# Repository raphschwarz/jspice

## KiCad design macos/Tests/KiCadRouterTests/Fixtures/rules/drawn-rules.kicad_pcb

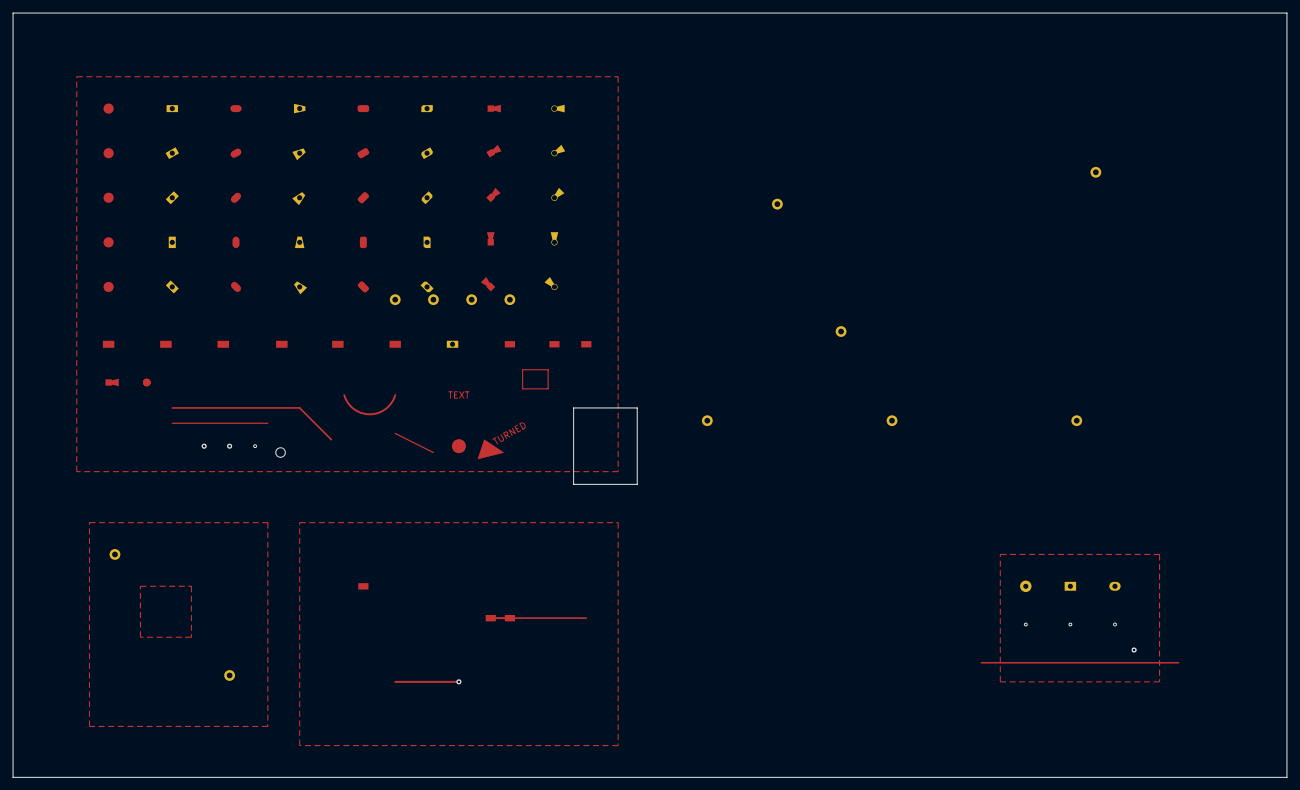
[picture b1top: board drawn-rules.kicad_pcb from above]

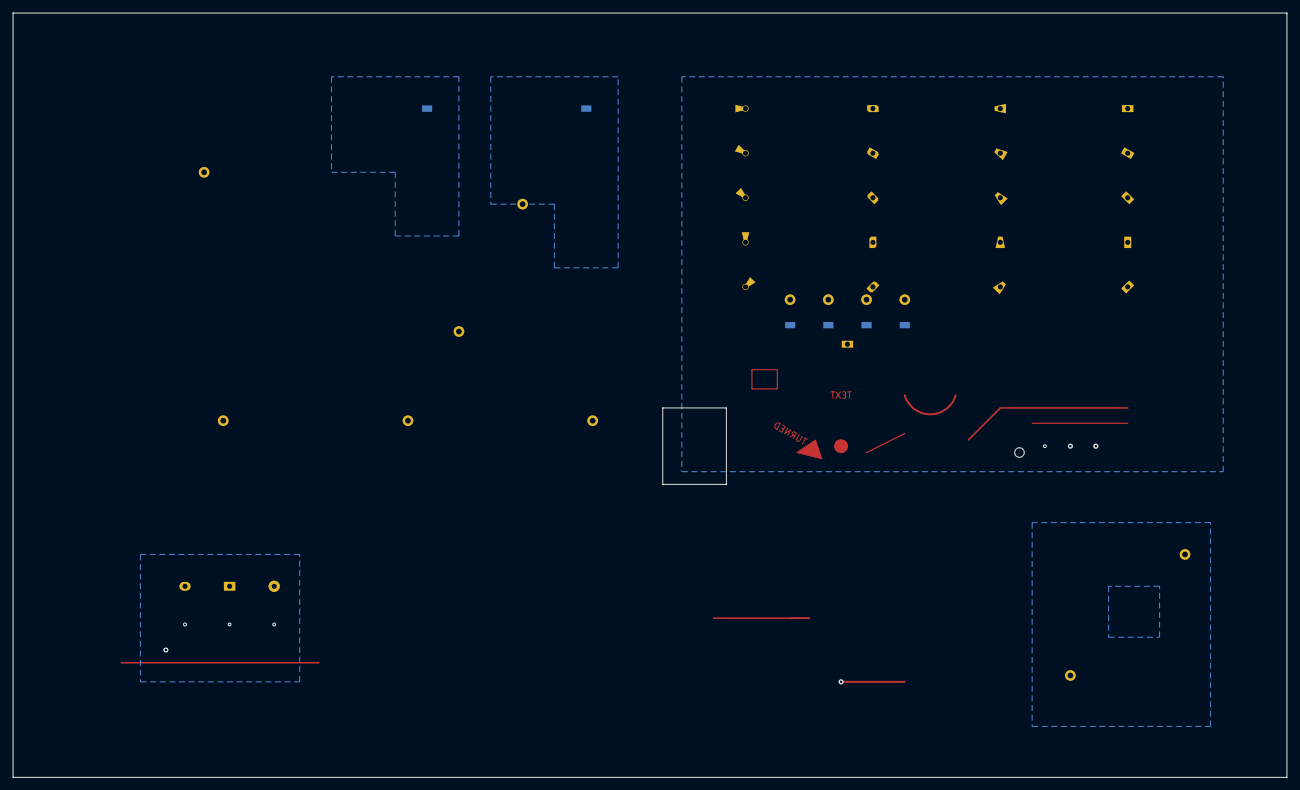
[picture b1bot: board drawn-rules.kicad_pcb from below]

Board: 4 copper layers, 200.0 x 120.0 mm, 78 parts (6 on the bottom side), 3 nets.

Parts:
H1, H2: (no value)
I0, I1, I2: (no value)
M1, M2: (no value)
NT1: (no value)
O0, O1, O2, O3, O4, O5, O6, O9, O10, O11, O12, O13, O14: (no value)
P1, P2, P3: (no value)
Q0, Q1, Q2: (no value)
S1, S2: (no value)
T00, T01, T02, T03, T04, T10, T11, T12, T13, T14, T20, T21, T22, T23, T24, T30, T31, T32, T33, T34, T40, T41, T42, T43, T44, T50, T51, T52, T53, T54, T60, T61, T62, T63, T64, T70, T71, T72, T73, T74: (no value)
V0, V1, V2, V3: (no value)
W0, W1, W2, W3: (no value)
Z1: (no value)

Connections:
GND: I0.1, I1.1, I2.1, M1.1, NT1.1, O0.1, O1.1, O2.1, O3.1, O4.1, O5.1, O6.1, O9.1, O13.1, O14.1, P2.1, P3.1, S1.1, S2.1, T00.1, T01.1, T02.1, T03.1, T04.1, T10.1, T11.1, T12.1, T13.1, T14.1, T20.1, T21.1, T22.1, T23.1, T24.1, T30.1, T31.1, T32.1, T33.1, T34.1, T40.1, T41.1, T42.1, T43.1, T44.1, T50.1, T51.1, T52.1, T53.1, T54.1, T60.1, T61.1, T62.1, T63.1, T64.1, T70.1, T71.1, T72.1, T73.1, T74.1, Z1.1
SIG: M2.1, NT1.2, O10.1, O11.1, O12.1
VCC: P1.1, Q0.1, Q1.1, Q2.1, V0.1, V1.1, V2.1, V3.1, W0.1, W1.1, W2.1, W3.1

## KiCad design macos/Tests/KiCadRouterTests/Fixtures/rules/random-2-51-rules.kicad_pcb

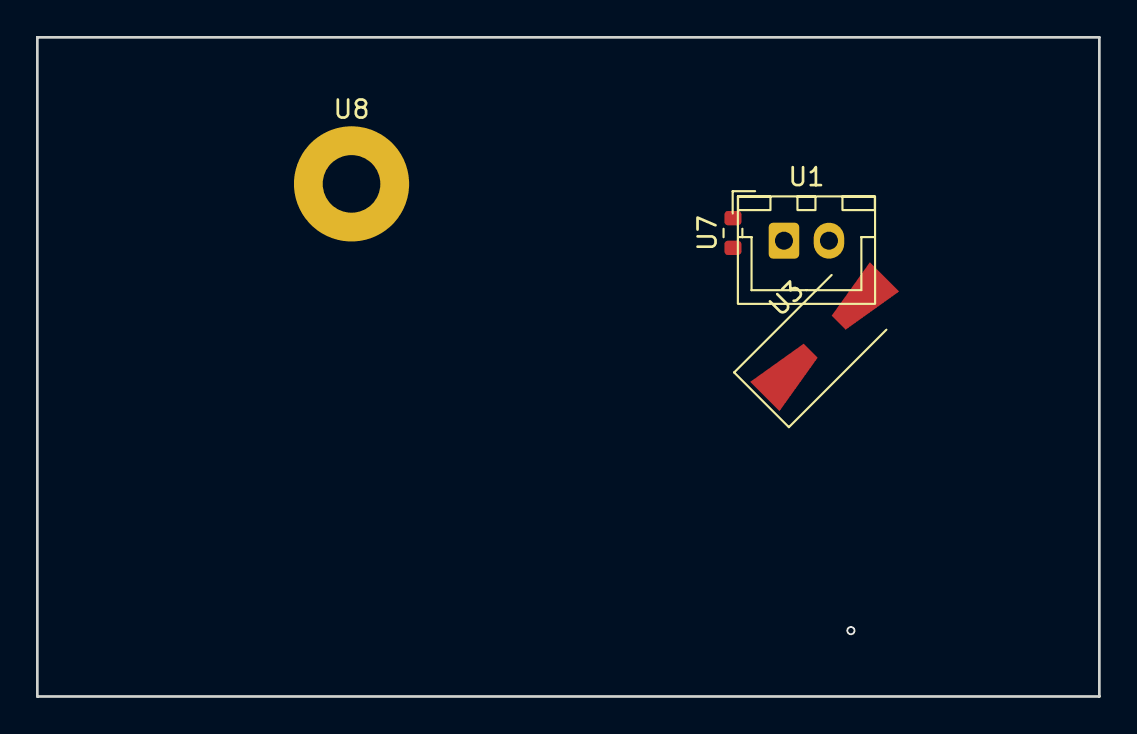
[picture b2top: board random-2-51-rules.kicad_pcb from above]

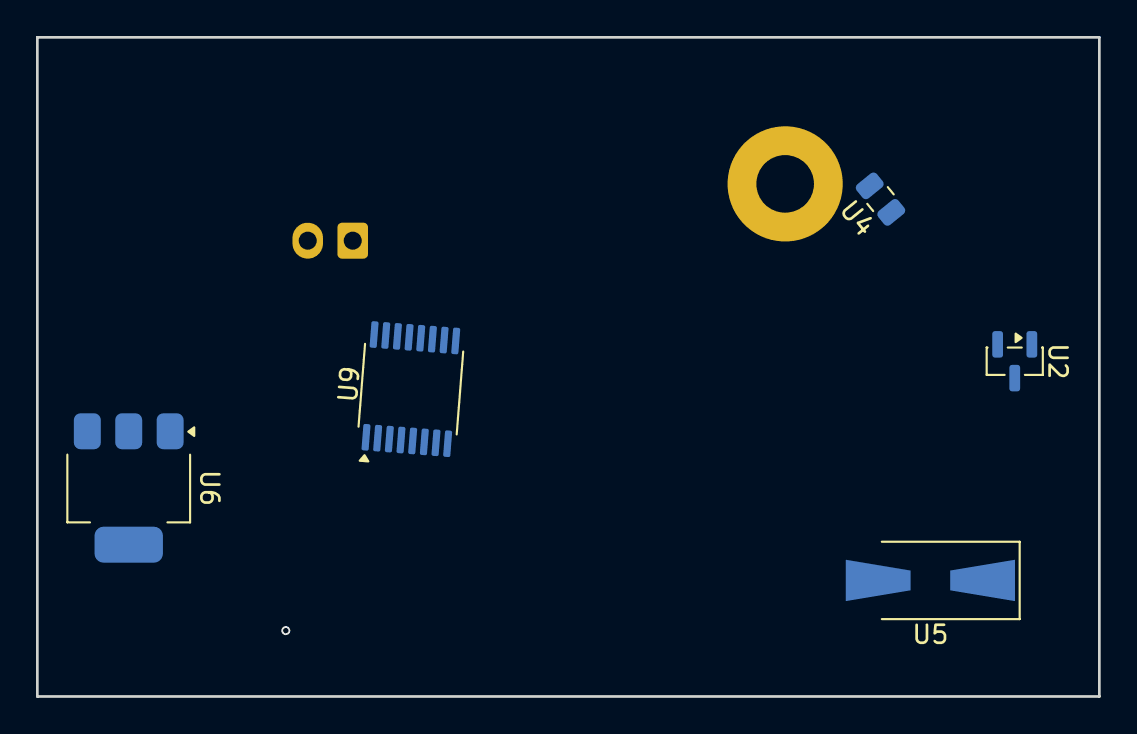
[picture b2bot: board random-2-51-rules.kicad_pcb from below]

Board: 4 copper layers, 59.0 x 36.6 mm, 9 parts (5 on the bottom side), 6 nets.

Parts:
U1: JST_XH_B2B-XH-A_1x02_P2.50mm_Vertical
U2: SOT-23
U3, U5: D_SMA-SMB_Universal_Handsoldering
U4: C_0805_2012Metric
U6: SOT-223-3_TabPin2
U7: R_0603_1608Metric
U8: MountingHole_3.2mm_M3_Pad
U9: TSSOP-16_4.4x5mm_P0.65mm

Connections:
GND: U7.1, U9.2, U9.7, U9.8
N2: U1.2, U9.1
PWR_5V: U9.10, U9.11
SIG1: U6.1, U6.2, U7.2, U9.6
SIG2: U2.2, U6.2
VCC: U2.3, U3.1, U3.2, U9.15

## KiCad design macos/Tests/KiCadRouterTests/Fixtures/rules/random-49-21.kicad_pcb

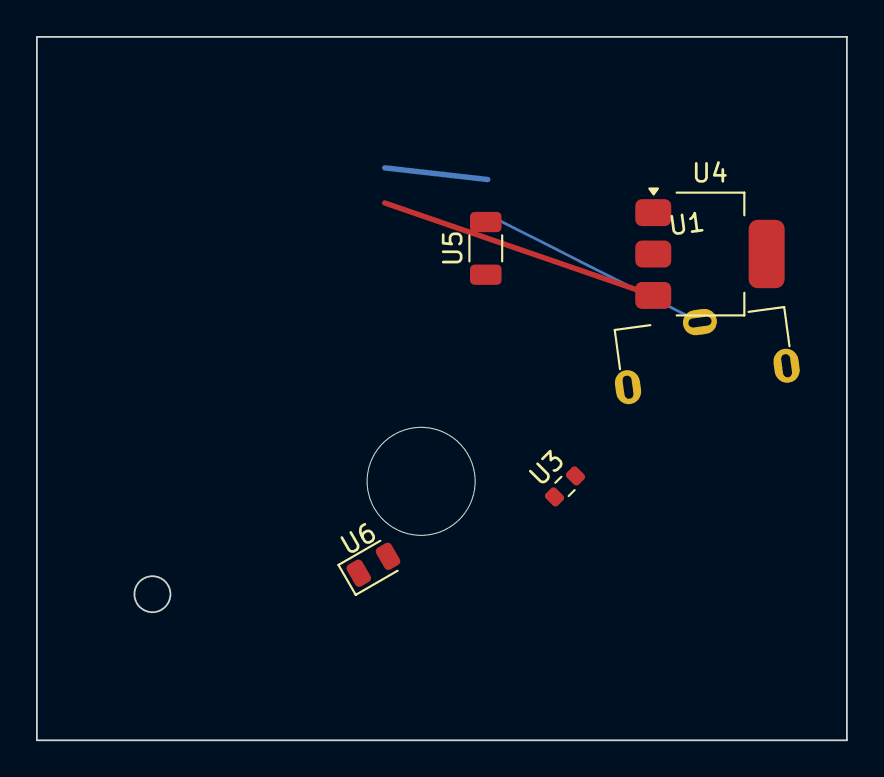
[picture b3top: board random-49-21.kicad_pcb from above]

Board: 2 copper layers, 45.0 x 39.1 mm, 6 parts (1 on the bottom side), 6 nets.

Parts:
U1: BatteryHolder_Keystone_590
U2: TSSOP-16_4.4x5mm_P0.65mm
U3: R_0603_1608Metric
U4: SOT-223-3_TabPin2
U5: R_1206_3216Metric
U6: LED_0805_2012Metric

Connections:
/net3: U2.1, U2.7, U2.9
/sub/clk: U1.1, U2.13, U3.1, U3.2
N1: U2.12, U5.1, U6.1
N3: U1.1, U2.16, U6.2
PWR1: U2.4, U4.3, U5.2
SIG1: U2.2, U2.6, U2.14, U2.15, U4.2

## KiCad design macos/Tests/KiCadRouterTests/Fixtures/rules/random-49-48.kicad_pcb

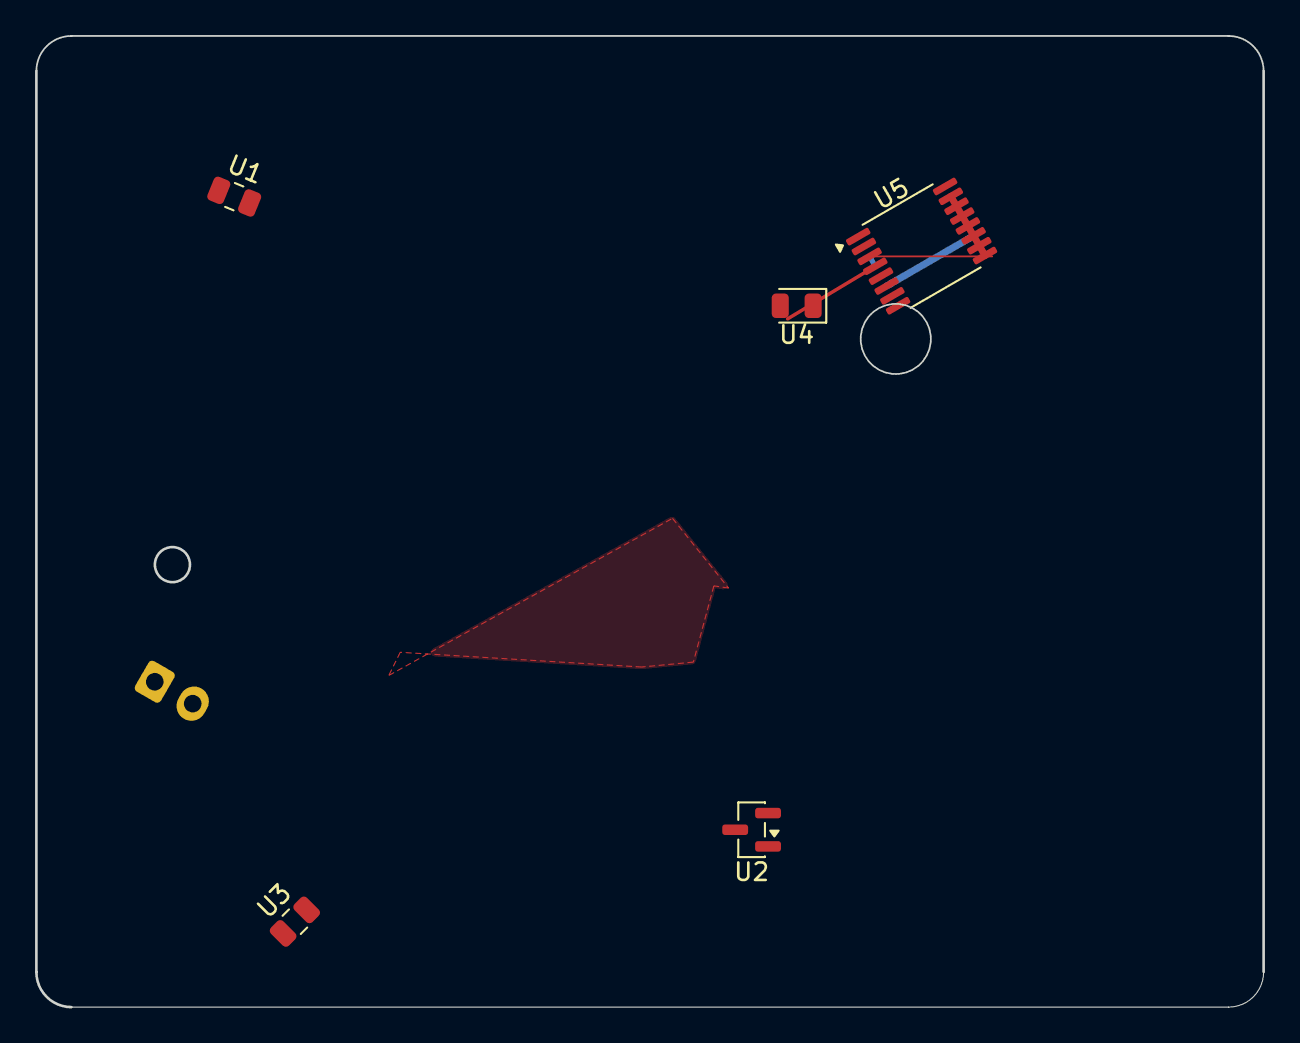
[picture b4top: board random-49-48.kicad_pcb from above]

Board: 2 copper layers, 70.0 x 55.4 mm, 6 parts (1 on the bottom side), 6 nets.

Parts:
U1, U3: C_0805_2012Metric
U2: SOT-23
U4: LED_0805_2012Metric
U5: TSSOP-16_4.4x5mm_P0.65mm
U6: JST_XH_B2B-XH-A_1x02_P2.50mm_Vertical

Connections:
D7: U2.1, U2.2, U5.13, U6.2
D12: U3.2, U5.14
N1: U4.1, U5.1, U5.4, U5.6, U5.8, U6.1
N3: U2.3, U5.12
PWR1: U3.1, U5.5, U5.7, U5.16
SIG1: U1.1, U4.2

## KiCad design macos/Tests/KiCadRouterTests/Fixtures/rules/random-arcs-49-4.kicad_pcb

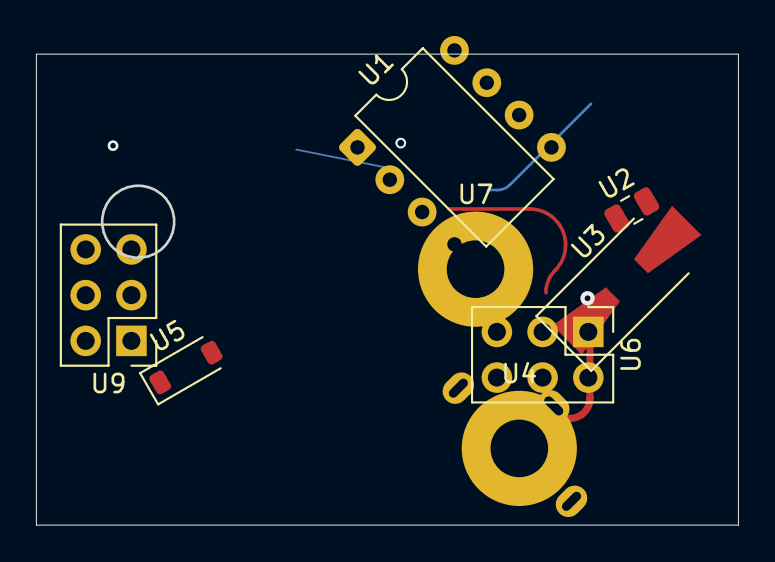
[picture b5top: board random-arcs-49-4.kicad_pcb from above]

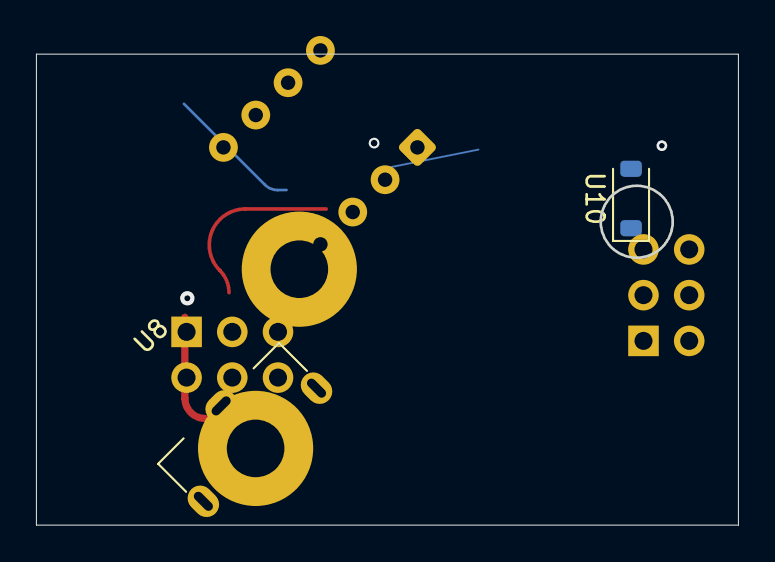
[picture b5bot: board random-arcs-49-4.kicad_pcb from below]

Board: 2 copper layers, 39.0 x 26.2 mm, 10 parts (2 on the bottom side), 9 nets.

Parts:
U1: DIP-8_W7.62mm
U2: C_0805_2012Metric
U3: D_SMA-SMB_Universal_Handsoldering
U4, U7: MountingHole_3.2mm_M3_Pad
U5, U10: D_SOD-123
U6, U9: PinHeader_2x03_P2.54mm_Vertical
U8: BatteryHolder_Keystone_590

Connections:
/net3: U1.5, U3.1
/sub/clk: U6.5, U10.1
GND: U1.3, U1.4, U2.1, U8.1
N1: U1.1, U2.2, U5.1
N3: U8.1, U10.2
PWR1: U1.7, U5.2, U8.1, U9.4, U9.5
PWR_5V: U6.2, U6.6, U9.2, U9.6
SIG1: U6.4, U7.1
VCC: U1.6, U4.1, U6.3

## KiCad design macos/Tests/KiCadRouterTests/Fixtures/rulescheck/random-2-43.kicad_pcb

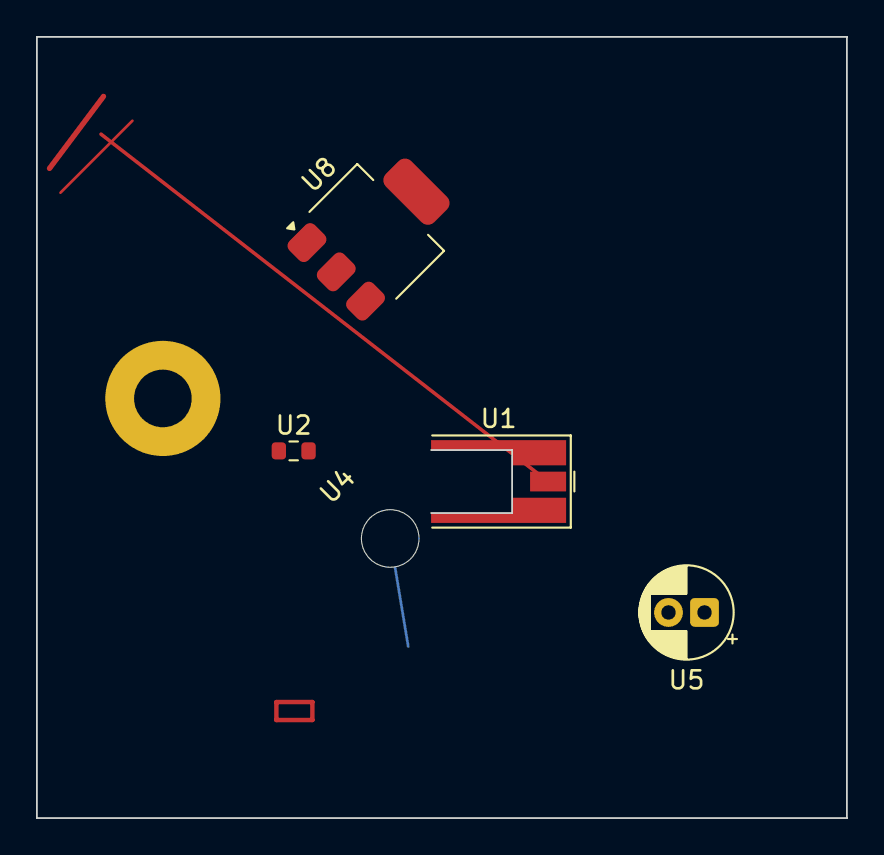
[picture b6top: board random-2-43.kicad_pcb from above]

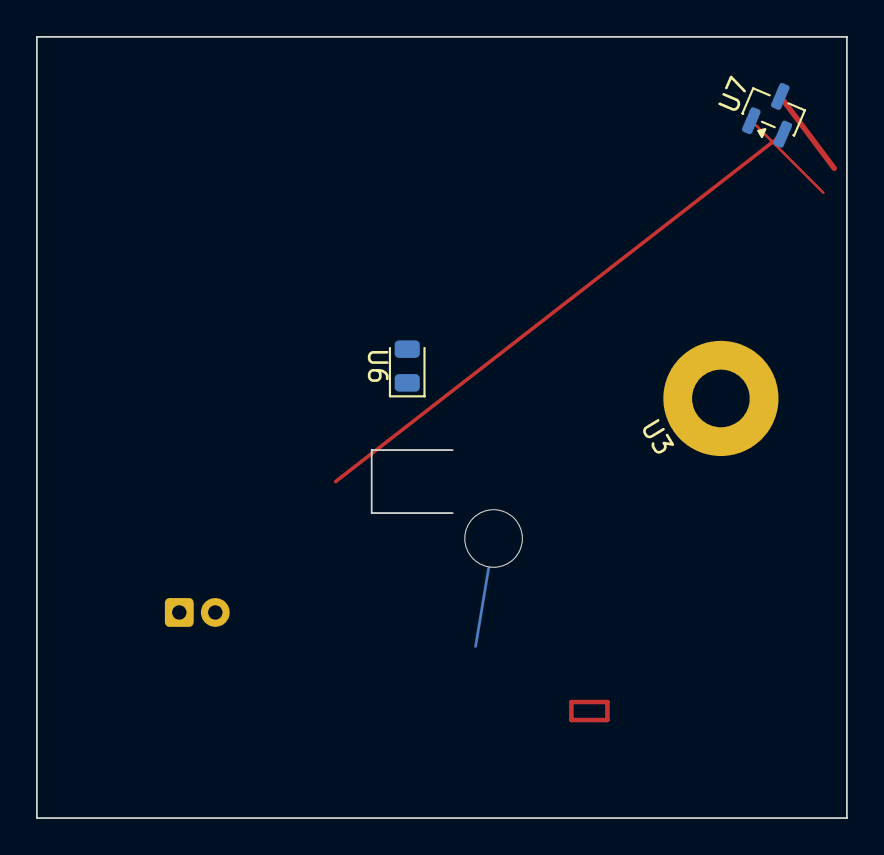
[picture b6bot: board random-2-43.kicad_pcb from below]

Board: 4 copper layers, 45.0 x 43.4 mm, 8 parts (3 on the bottom side), 3 nets.

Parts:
U1: MMCX_Molex_73415-0961_Horizontal_0.8mm-PCB
U2: R_0603_1608Metric
U3: MountingHole_3.2mm_M3_Pad
U4: MountingHole_3.2mm_M3
U5: CP_Radial_D5.0mm_P2.00mm
U6: LED_0805_2012Metric
U7: SOT-23
U8: SOT-223-3_TabPin2

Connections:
D12: U6.1, U7.2
N1: U3.1, U6.2
N3: U2.2, U7.3, U8.3

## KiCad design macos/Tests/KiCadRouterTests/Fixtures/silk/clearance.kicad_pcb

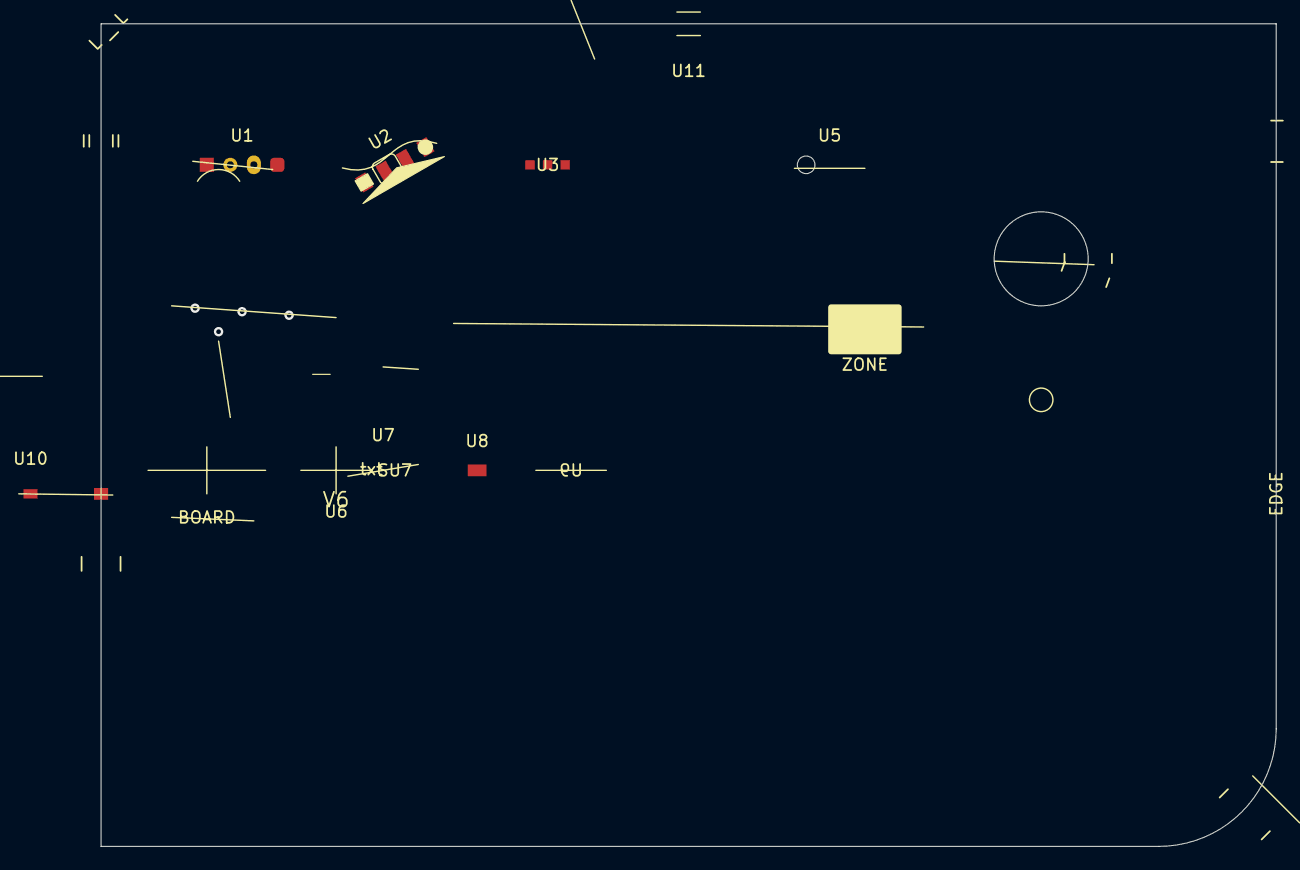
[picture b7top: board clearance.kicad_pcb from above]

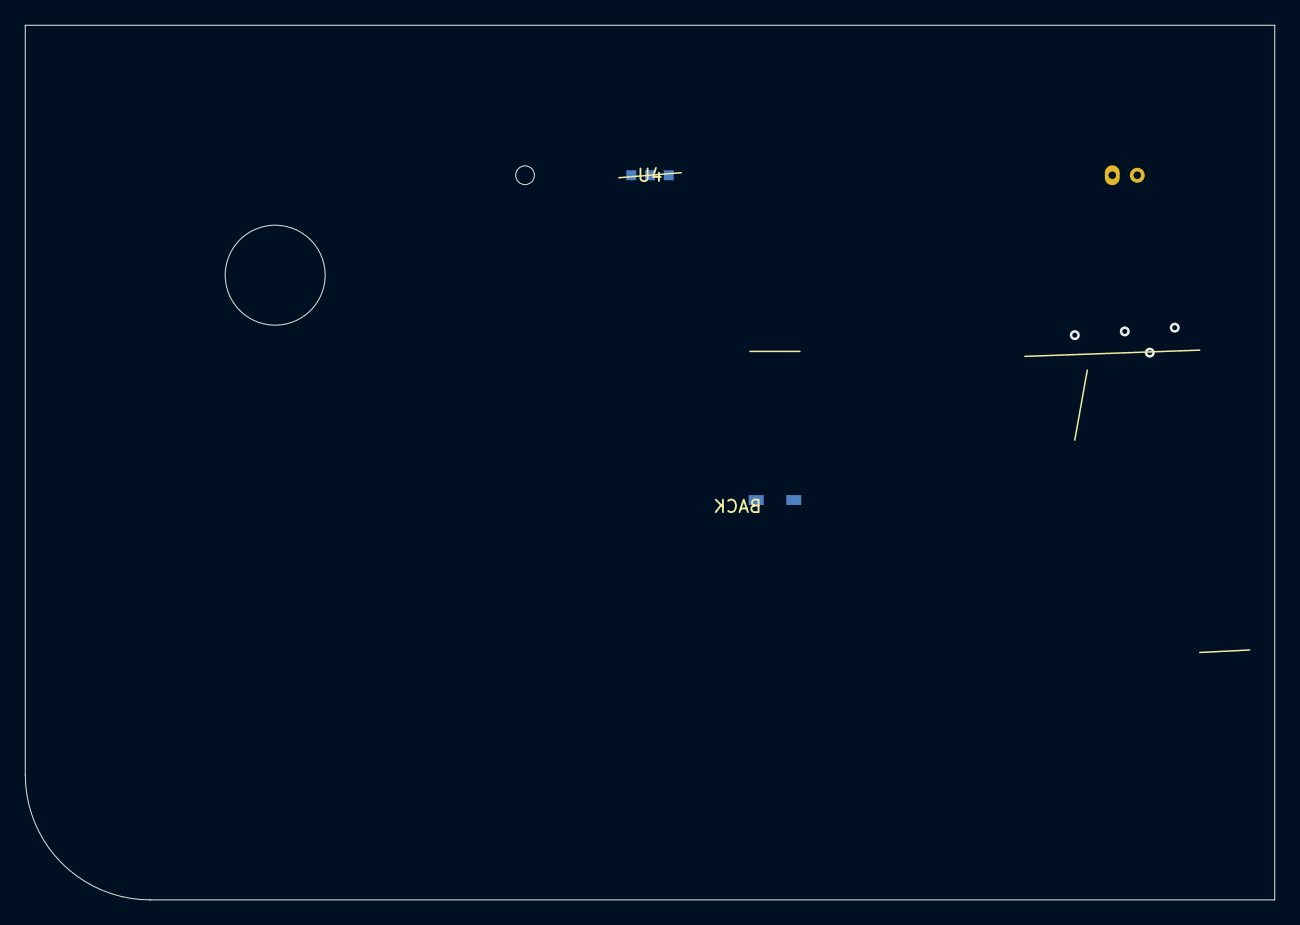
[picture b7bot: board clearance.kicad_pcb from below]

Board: 2 copper layers, 100.0 x 70.0 mm, 11 parts (2 on the bottom side), 2 nets.

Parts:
U1: V1
U2: V2
U3: V3
U4: V4
U5: V5
U6: V6
U7: V7
U8: V8
U9: V9
U10: V10
U11: V11

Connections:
GND: U2.2, U2.4, U9.2
SIG: U2.1, U2.3, U3.1, U3.2, U3.3, U4.1, U4.2, U4.3, U8.1, U9.1, U10.1, U10.2
